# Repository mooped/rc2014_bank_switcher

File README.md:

# RC2014 Bank Switcher
Implements a minimal bank switcher to swap the RC2014 boot ROM for 32kB of RAM with 1x 74HCT00, 1x 74LS32, and 1x 74HCT04.

Designed to work with one standard RC2014 ROM module and two standard RC2014 RAM modules.

One RAM module and the bank switcher are installed in any slot in the centre of the backplane (slots 3-8). The ROM and the second RAM module need their A15 signal replaced with output from the bank switcher. This is most easily achieved through the jumpers on the RC2014 backplane between slots 2 and 3 and slots 6 and 7.

In my setup the extra RAM is installed in slot 2 and the ROM installed in slot 7, any RC2014 board that does not require A15 (eg. the serial board, IO board, clock board) can be installed in slots 1 and 8. Jumpers A14 to A0 and D0 to D7 are bridged on both sides of the backplane. Pin headers are installed in Tx, Rx and the four auxilliary bus lines. The replacement A15 signals for the ROM and the extra RAM are brought out to Aux 1 and Aux 2 by setting jumpers on the bank switcher board. Aux 1 is then connected to A15 on the slot 2 side of the left A15 jumper. Aux 2 is conneccted to A15 on the slot 7 side of the right A15 jumper.

The ROM and RAM A15 signals are also brought out to a header at the A15 end of the bank switcher board to simplify alternative setups.

ROM is mapped as usual (0x0000 to 0x1fff) on reset. Any write to IO address 0xf0 to 0xff will disable the ROM and enable a standard RC2014 32kB RAM module (0x000 to 0x7fff). It is not possible to switch the ROM back in except on a reset.

The gerbers in v1.0 have been tested and work correctly. Later versions have not been built or tested. There is a minor error in v1.0: the hole for pin A8 of the RC2014 bus header is too small for a standard header. This signal is not used so the problem is resolved by simply removing the pin from the header.

v1.0 - Initial revision.

v1.1 - Enlarged A8 of the RC2014 bus header. Enlarged holes for P3 (auxilliary A15 output header).

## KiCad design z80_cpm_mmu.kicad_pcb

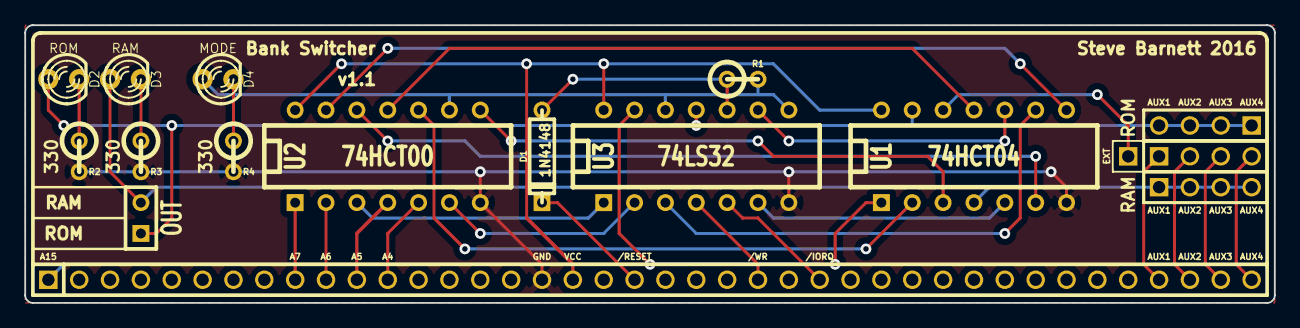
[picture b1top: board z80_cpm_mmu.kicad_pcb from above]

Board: 2 copper layers, 102.9 x 22.9 mm, 17 parts (0 on the bottom side), 32 nets.

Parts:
D1: 1N4148; D3
D2: ROM; LED-3MM
D3: RAM; LED-3MM
D4: MODE; LED-3MM
P1: BUS; SIL-40
P2: ROM; PIN_ARRAY_4x1
P3: OUT; SIL-2
P4: RAM; PIN_ARRAY_4x1
P5: AUX; PIN_ARRAY_4x1
P6: EXT; PIN_ARRAY_1
R1: 1K2; R1
R2, R3, R4: 330; R1
U1: 74HCT04; DIP-14__300
U2: 74HCT00; DIP-14__300
U3: 74LS32; DIP-14__300

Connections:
//IORQ: P1.26, U3.5
//WR: P1.24, U3.4
/A4: P1.12, U2.5
/A5: P1.11, U2.4
/A6: P1.10, U2.2
/A7: P1.9, U2.1
/A15: P1.1, U1.1, U3.13
/AUX1: P1.37, P5.1
/AUX2: P1.38, P5.2
/AUX3: P1.39, P5.3
/AUX4: P1.40, P5.4
/RAM_A15: D3.1, P3.2, P4.1, P4.2, P4.3, P4.4, U1.4
/RESET: D1.2, P1.20
/ROM_A15: D2.1, P2.1, P2.2, P2.3, P2.4, P3.1, U1.13, U3.11
/mode: D4.1, R1.2, U2.9, U3.8, U3.12
GND: P1.17, R2.2, R3.2, R4.2, U1.7, U2.7, U3.7
unnamed: U1.10, U3.9
unnamed: U1.11, U2.11
unnamed: U1.8, U2.13
unnamed: U1.6, U2.12
unnamed: D1.1, R1.1, U3.10
unnamed: D2.2, R2.1
unnamed: D4.2, R4.1
unnamed: D3.2, R3.1
unnamed: P6.1, U1.12
unnamed: U1.3, U2.8
unnamed: U1.2, U2.10
unnamed: U1.5, U3.6
unnamed: U2.3, U3.1
unnamed: U1.9, U3.3
unnamed: U2.6, U3.2
VCC: P1.18, U1.14, U2.14, U3.14

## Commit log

2016-06-13 Plot v1.0
2016-06-13 Rework silk screen on v1.0
2016-06-13 Fix IC references to be contiguous
2016-06-13 Begin work on v1.1 - fix size of bus pad 8
2016-06-29 Tweak readme.
2016-06-29 Enlarge holes for P3 header
2017-05-10 Add photos of the board
2017-05-10 Add images to the readme
